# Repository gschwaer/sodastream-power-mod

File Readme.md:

# SodaStream Power Mod

> Because the Internet of Things needed a smart soda maker.

There is (or was) a soda maker called "SodaStream Power". It has some buttons and LEDs and uses a servo to do the usual pushing motion that soda makers require. Mine was broken probably due to an [unfortunate design decision](#just-why--the-beginnings) (and me). So I thought: If I have to fix it by replacing the MCU either way, why not use a WIFI-enabled one? So I build a replacement PCB with an ESP8266. It even runs python! 😲

Disclaimer: It doesn't access the internet. But it could! -- But what for? Maybe I should blink the current time in morse code for each new soda, or add a cloud backend so I can better scale my soda making. 🤔😉

So what does it use WIFI for? Well, I can debug it remotely while it's standing in the kitchen. 😅

Otherwise it just does, well, make soda. Though I improved (imo) the [user interface](#ui-changes) a little.

> ℹ️ I did this project in 2019, but I rewrote the software and documentation in 2023, so some details might be lost to time.

## Hardware

The PCB was designed in KiCad and fabricated by JLCPCB in 2019.

Main components:
* MCU: `ESP8266-12F`
* I2C-Port-Expander: `PCF8574AN`
  * Note: The suffix `A` implies a different I2C base address than the version without the `A`. The non-`A` chip works as well (but needs a minor change in code). (Took me a few hours debugging before I realized I stared at the wrong data sheet.)
* 2x Hall Switch: `SI7205-B-00-IV`
* High Side Power Switch: `TPS22810DBVR`

### Known Design issues

1. In the first revision I made a mistake and wired the LEDs to $V_{in} = 6.5 V$ (with higher values for the current limiting resistor). I thought this way I could prevent wasting power in the $3.3 V$ regulator for the LED current. Yes, that was dumb, because the regulator is a linear regulator, so the resistor dumps the same amount of power. 🤦 But the LEDs wouldn't burden the regulator at least. Anyway, the actual problem was that the port expander did not have open drain ports. Instead, ports are actively driven to low and high ($3.3V$), so in the "off" state, the LEDs (+Resistor) would see $6.5V-3.3V = 3.2V$ and would just be dimmer. 😬 I fixed it by cutting a trace and botching a wire to have the LEDs use the $3.3V$ supply rail. I'm still using that version to date. In the KiCad project that mistake has been fixed. But I didn't reorder a PCB, so that change is untested.
2. I used the least sensible GPIOs (GPIO 0, 2) for IO. It worked ok in the end, though I later had a minor issue in micropython with PWM on GPIO2 after a soft reset, because GPIO2 is a boot select pin. But I was able to fix that in software and either way: in regular operation we don't soft reset.
3. I placed some components and traces beside the antenna. Probably not good, but works ok. There is unfortunately not much space for traces around this huge center cutout.

### Schematics

> ⚠️ Warning: The [KiCad project](./PCB/Sodastream/) was converted from an older KiCad version. I'm not sure if that worked ok.

For ease of use I made some screenshots of the schematics.

### Layout

I measured the holes and cutouts on the original PCB and used identical ones on my PCB so it fits in the PCB holder. The pink areas are markings for special locations in the PCB housing: Left and right areas are keep out zones for the housing's snap fit hooks. The area in the center marks where the cabling leaves the water-proof housing.

## Software

This project uses [micropython](https://github.com/micropython/micropython/) version `1.20.0` installed as per the [documentation for ESP8266](https://docs.micropython.org/en/v1.20.0/esp8266/quickref.html). Here's the command I used:
```bash
esptool.py --port "${DEV}" --baud 460800 write_flash --erase-all --flash_size=detect 0 ESP8266_GENERIC-20230426-v1.20.0.bin
```
The code in [`./src`](./src/) is compiled with `make`. You need `mpy-cross`, `pyboard.py`, and `gcc` (see [`Makefile`](./src/Makefile)).

After that we can upload the code with [micropython's `pyboard.py` tool](https://docs.micropython.org/en/v1.20.0/reference/pyboard.py.html). The configs [`./src/webrepl_cfg.py`](./src/webrepl_cfg.py) and [`./src/wifi_cfg.py`](./src/wifi_cfg.py) require some adjustments.

After that, you can access the board via WiFi in the browser at http://192.168.0.123:8266/ (or which ever IP your board got, mDNS would be an improvement here, see [Future Work](#future-work)).

### UI Changes

Iirc the vendor UI was very basic: We have 3 buttons and 3 LEDs, when you insert a bottle all LEDs light up. Then you press one of the buttons, you get a low, medium, or high dose of CO2 into the bottle. The different doses are solely achieved by opening the CO2 valve for different, fixed durations.

Of course, that is reasonable, but it's actually a not much of an improvement compared to the manual soda makers. The main drawbacks are:
1. You still need to press a button,
2. when the CO2 cylinder empties, its pressure drops. This means the simple relationship between the duration of opening the valve and the applied CO2 dose does not hold anymore.

Drawback 1. is easily mitigated by beginning to open the CO2 valve as soon as a bottle is inserted. This means I cannot select the dose beforehand. This can be remedied by allowing a change of the dose *during* the operation. (This change is only in effect for the current soda making.)

I solved drawback 2. by tracking the cylinder state. I redefined the buttons to mean *left = "less CO2"*, *right = "more CO2"* (*center = "abort/restart"*). If a selection is made after the soda making is done, it is saved for next time. So when the CO2 cylinder empties, I can adjust the valve opening duration step by step whenever a bottle is not pressured to the degree I want. I also added some more subtle functions, and a debug mode:

| Button | Held Down Before*             | Pressed While   | Pressed After    |
|--------|-------------------------------|-----------------|------------------|
| left   | (+right) reset cylinder state | less CO2 (temp) | less CO2 (saved) |
| right  | (+left) reset cylinder state  | more CO2 (temp) | more CO2 (saved) |
| middle | debug mode (WiFi)             | abort           | start again      |

Table: Effect of buttons (1) held down while inserting a bottle, (2) pressed while the soda making happens, and (3) pressed after the soda making is completed. (* If any button is held down while a bottle is inserted, the CO2 valve stays closed. So resetting the cylinder state and entering debug mode can be done without wasting CO2.)

### Issues

I ran into some issues:

WebREPL:
* It's annoying to figure out the boards IP address. I currently check my router. But mDNS would be an obvious improvement.
* I regularly forget that when logging in via WebREPL, my python code is still running. Remember: after logging in, do `ctrl+c` to end the running program.

Boot Time:
* Boot time increases every time you overwrite a python file that is loaded at boot! I assume that has something to do with the flash filesystem trying to prevent wear. Maybe it does some copy-on-write with a linked list to traverse to the latest valid chunk? idk
  * If I remember correctly (! I didn't confirm it again !), you can reset this behavior by reformatting the flash (after that you have to reupload all files):
    ```python
    import uos
    from flashbdev import bdev
    uos.VfsLfs2.mkfs(bdev)
    vfs = uos.VfsLfs2(bdev)
    uos.mount(vfs, "/")
    ```
* I am using the following boot flow: `boot.py` -...-> `main.py` -> `sprudler.mpy`. That is mainly because `boot.py` and `main.py` cannot be compiled `.mpy` files. In `boot.py` I only put everything that I want done ASAP and `main.py` only `import`s the compiled `.mpy` file. I experimented a lot while trying to bring down boot time. I did not save the experiment results, but this solution got the best results for my use-case.
* The servo has three positions: (1) valve closed & bottle unlocked, (2) valve closed & bottle locked, (3) valve open & bottle locked. In `boot.py` I move the servo to the second (2) position. While the servo is moving to that position, we load the rest of the software and regular operation begins. This reduces the effective delay until operation begins.
* To optimize the compiled `.mpy` file, I experimented with regular global constants, constants marked with `const()`, and plain inserted constants. I'm not entirely sure what worked best, because while experimenting I also stumbled upon the issue above. Iirc boot time was best with inserted constants. So I stuck with that and added a preprocessor step using regular C preprocessor defines like `#define MY_CONST 123` in `sprudler.py`. (They get slightly garbled by the `black` formatter, but meh, I just undo this in the `Makefile`. Not elegant but works ok.)

WiFi AP:
* The WiFi AP does not work on my board with micropython `1.20.0`, so I disabled it (see [issue](https://github.com/micropython/micropython/issues/9226#issuecomment-1718269312)).
  * To prevent the board from boot looping after flashing, connect via serial and spam-paste the following into the terminal (including the newline):
    ```
    import network; network.WLAN(network.AP_IF).active(False)

    ```
    After some tries it will hit after the REPL becomes ready but before the AP is set up and the boot loop stops.

PWM:
* The servo is twitching if WiFi is enabled: The ESP8266 does not have hardware PWM outputs, so micropython does software PWM. WiFi will add a lot of load, which adds occasional lag on the software PWM timer handler. Ok for me, I only use WiFi in debug mode, where I can live with some servo twitching.

## Just Why?! / The Beginnings

Why am I doing this? Well, the electronics of my soda maker "broke", here's what happened:

The original circuitry has a tilt switch. It is just a conductive ball resting on two parallel wires, thus shorting the connection. The whole thing is in a black rectangular plastic housing with enough head room so the ball can slightly move upwards. If the PCB is flipped upside down the ball will fall away from the wires (now an open circuit) and the MCU will register that.

It turns out, if the device is on, you flip it upside down, and press any button, the MCU will go into an error state and blink the LEDs. Okay fine, maybe we just don't want our precious soda on the floor. But there is **no** way to get out of this error state! Not power cycling, no combination of button presses, short and long presses, with or without a bottle inserted, I tried everything I could think of. So ... this device just bricks itself? 🙃

Side note: If you are that kind of person (like me) who wants to know how devices work, and like to open them up to find out, you sometimes move parts aside, like for example **the PCB**, and maybe even let it dangle **upside down** on the side since the cables are so short...

However, I cannot be 100% certain that this is what bricked it. But there is a tilt switch on the PCB, it's connected to the controller, and the device went into the error state once I operated it with the PCB hanging upside down. But it could have been something else I did, who knows.

Why would the manufacturer do that? Not sure, maybe it is due to a regulation? CO2 in compressed gas cylinders is actually liquid. So from what I read, if you operate the valve while the CO2 cylinder is upside down it will spill the liquid CO2 which is very cold due to the drop in pressure. Maybe they wanted (or had) to prevent this hazard. (But why permanently!?)

## Future Work

- Add mDNS, so I don't need to look up the IP address.
  - https://github.com/vaudric/micropython/tree/main/mdns
  - https://github.com/nickovs/slimDNS
- Measure bottle pressure with a pressure sensor?

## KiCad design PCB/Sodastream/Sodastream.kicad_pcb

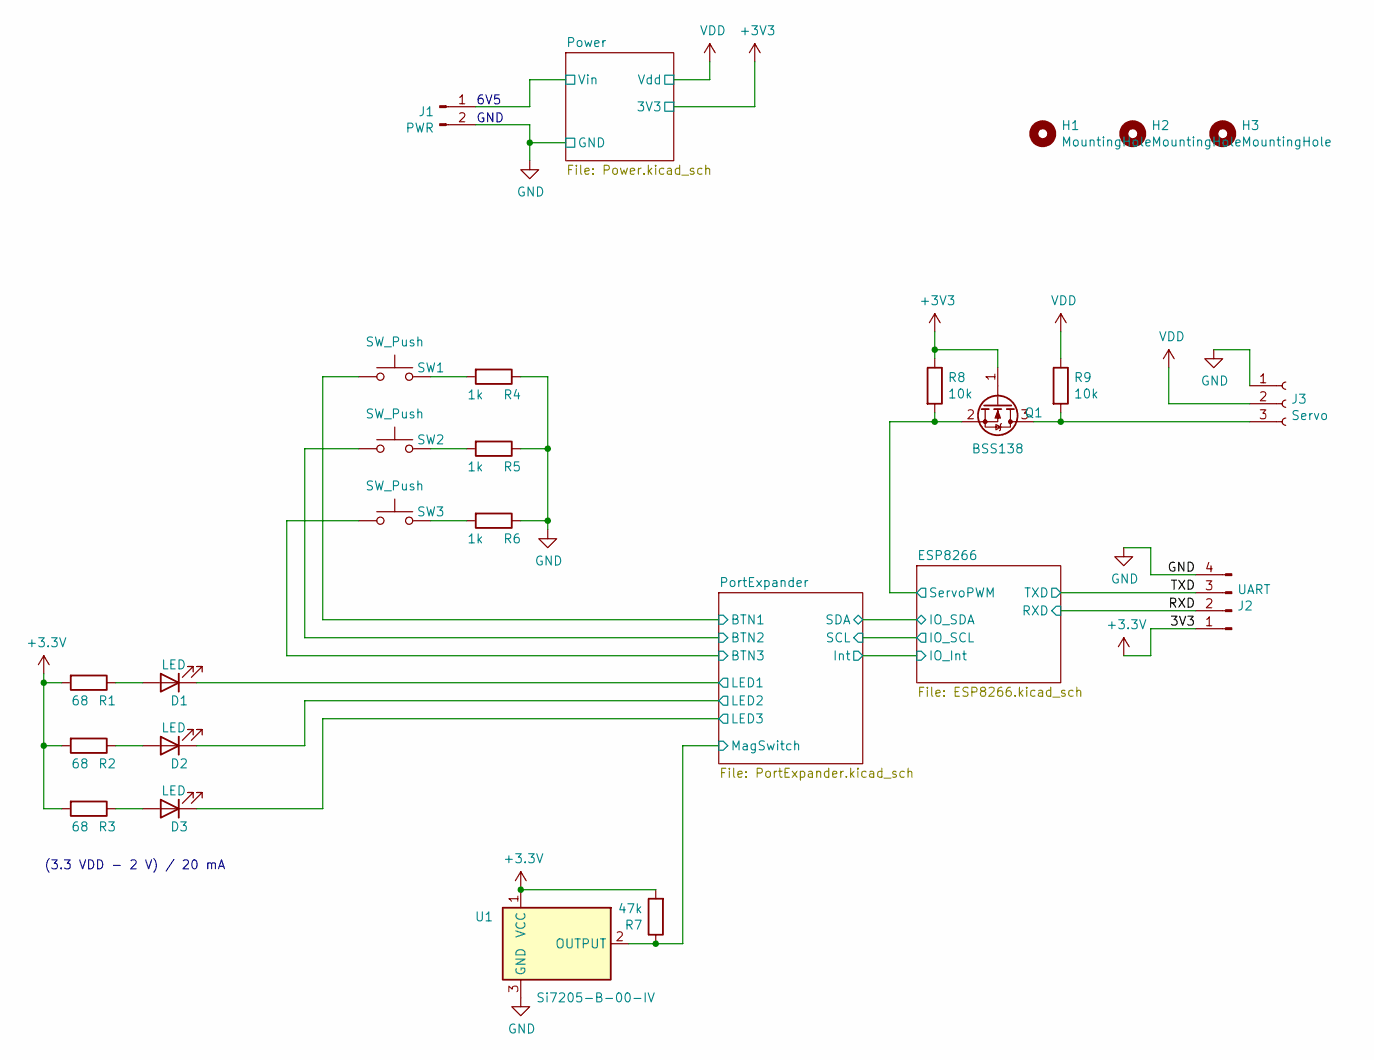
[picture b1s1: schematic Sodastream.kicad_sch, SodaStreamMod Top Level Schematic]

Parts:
D1, D2, D3: LED; LED_SMD_SideView_3.0x1.0x2.0_2+1pin
H1, H2, H3: MountingHole; MountingHole_3.2mm_M3
J1: PWR; PinHeader_1x02_P2.54mm_Vertical
J2: UART; PinHeader_1x04_P2.54mm_Vertical
J3: Servo; PinHeader_1x03_P2.54mm_Vertical
Q1: BSS138; SOT-23
R1, R2, R3: 68; R_1206_3216Metric_Pad1.42x1.75mm_HandSolder
R4, R5, R6: 1k; R_1206_3216Metric_Pad1.42x1.75mm_HandSolder
R7: 47k; R_1206_3216Metric_Pad1.42x1.75mm_HandSolder
R8, R9: 10k; R_1206_3216Metric_Pad1.42x1.75mm_HandSolder
SW1, SW2, SW3: SW_Push; SW_WE_6x6mm
U1: Si7205-B-00-IV; SOT-23

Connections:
+3V3: J2.1, Q1.1 (G), R1.2, R2.2, R3.2, R7.2, R8.1, U1.1 (VCC); also elsewhere on the board
/ESP8266/ServoPWM: Q1.2 (S), R8.2; also elsewhere on the board
/PortExpander/BTN1: SW1.1; also elsewhere on the board
/PortExpander/BTN2: SW2.1; also elsewhere on the board
/PortExpander/BTN3: SW3.1; also elsewhere on the board
/PortExpander/LED1: D1.1 (K); also elsewhere on the board
/PortExpander/LED2: D2.1 (K); also elsewhere on the board
/PortExpander/LED3: D3.1 (K); also elsewhere on the board
/PortExpander/MagSwitch: R7.1, U1.2 (OUTPUT); also elsewhere on the board
/Power/Vin: J1.1; also elsewhere on the board
/RXD: J2.2; also elsewhere on the board
/TXD: J2.3; also elsewhere on the board
GND: J1.2, J2.4, J3.1, R4.1, R5.1, R6.1, U1.3 (GND); also elsewhere on the board
unnamed: D1.2 (A), R1.1
unnamed: D2.2 (A), R2.1
unnamed: D3.2 (A), R3.1
unnamed: J3.3, Q1.3 (D), R9.2
unnamed: R4.2, SW1.2
unnamed: R5.2, SW2.2
unnamed: R6.2, SW3.2
VDD: J3.2, R9.1; also elsewhere on the board

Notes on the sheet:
(3.3 VDD - 2 V) / 20 mA
GND
6V5

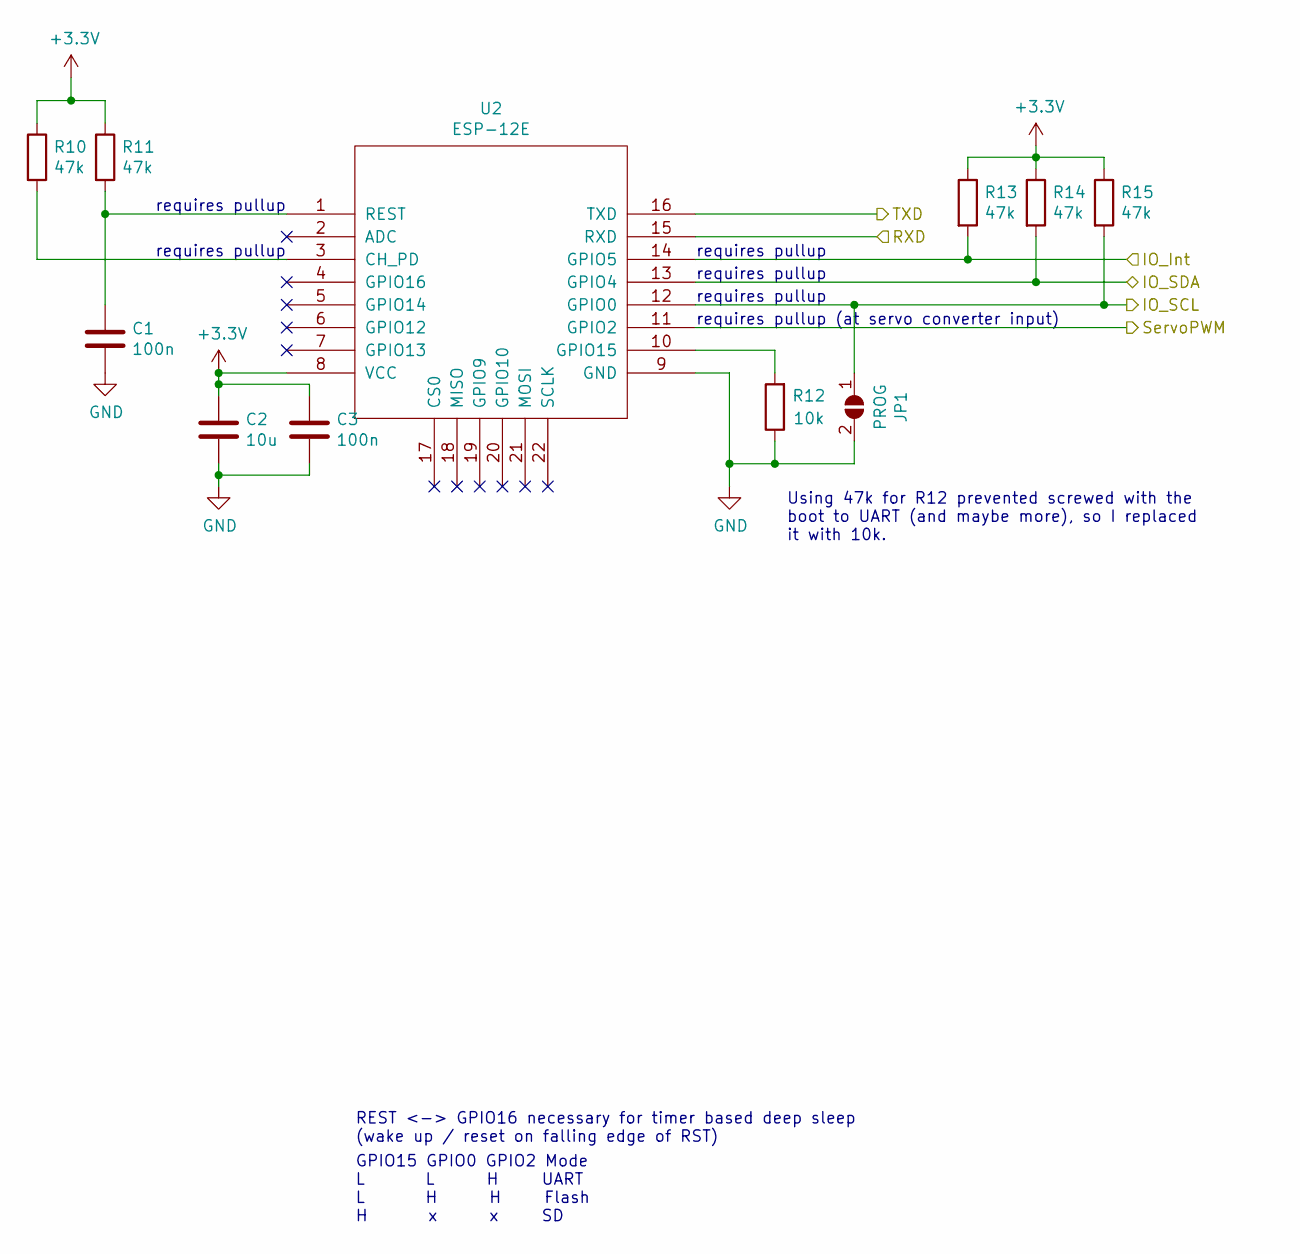
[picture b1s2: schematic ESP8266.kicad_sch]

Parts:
C1, C3: 100n; C_0805_2012Metric_Pad1.15x1.40mm_HandSolder
C2: 10u; C_0805_2012Metric_Pad1.15x1.40mm_HandSolder
JP1: PROG; SolderJumper-2_P1.3mm_Open_RoundedPad1.0x1.5mm
R10, R11, R13, R14, R15: 47k; R_1206_3216Metric_Pad1.42x1.75mm_HandSolder
R12: 10k; R_1206_3216Metric_Pad1.42x1.75mm_HandSolder
U2: ESP-12E; ESP-12E_SMD

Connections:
+3V3: C2.1, C3.1, R10.1, R11.1, R13.1, R14.1, R15.1, U2.8 (VCC); also elsewhere on the board
/ESP8266/IO_Int: R13.2, U2.14 (GPIO5); also elsewhere on the board
/ESP8266/IO_SCL: JP1.1 (A), R15.2, U2.12 (GPIO0); also elsewhere on the board
/ESP8266/IO_SDA: R14.2, U2.13 (GPIO4); also elsewhere on the board
/ESP8266/ServoPWM: U2.11 (GPIO2); also elsewhere on the board
/RXD: U2.15 (RXD); also elsewhere on the board
/TXD: U2.16 (TXD); also elsewhere on the board
GND: C1.2, C2.2, C3.2, JP1.2 (B), R12.1, U2.9 (GND); also elsewhere on the board
unnamed: C1.1, R11.2, U2.1 (REST)
unnamed: R10.2, U2.3 (CH_PD)
unnamed: R12.2, U2.10 (GPIO15)

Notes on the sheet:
requires pullup
requires pullup (at servo converter input)
Using 47k for R12 prevented screwed with the boot to UART (and maybe more), so I replaced it with 10k.
REST <-> GPIO16 necessary for timer based deep sleep (wake up / reset on falling edge of RST)
GPIO15 GPIO0 GPIO2 Mode L L H UART L H H Flash H x x SD

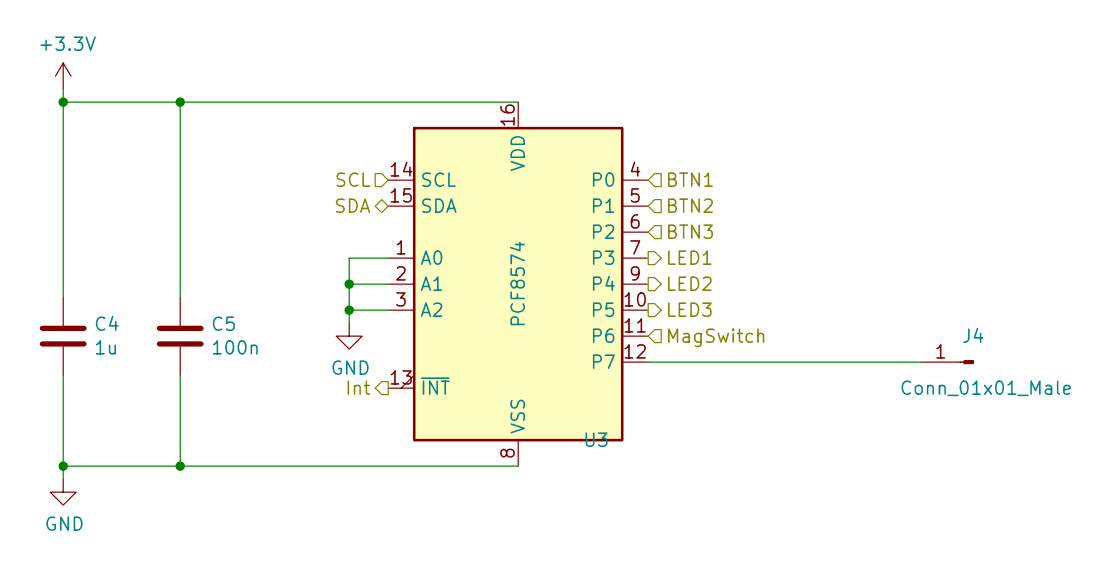
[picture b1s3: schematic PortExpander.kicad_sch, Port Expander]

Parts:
C4: 1u; C_0805_2012Metric_Pad1.15x1.40mm_HandSolder
C5: 100n; C_0805_2012Metric_Pad1.15x1.40mm_HandSolder
J4: Conn_01x01_Male; PinHeader_1x01_P2.54mm_Vertical
U3: PCF8574; DIP-16_W7.62mm

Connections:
+3V3: C4.1, C5.1, U3.16 (VDD); also elsewhere on the board
/ESP8266/IO_Int: U3.13 (~INT); also elsewhere on the board
/ESP8266/IO_SCL: U3.14 (SCL); also elsewhere on the board
/ESP8266/IO_SDA: U3.15 (SDA); also elsewhere on the board
/PortExpander/BTN1: U3.4 (P0); also elsewhere on the board
/PortExpander/BTN2: U3.5 (P1); also elsewhere on the board
/PortExpander/BTN3: U3.6 (P2); also elsewhere on the board
/PortExpander/LED1: U3.7 (P3); also elsewhere on the board
/PortExpander/LED2: U3.9 (P4); also elsewhere on the board
/PortExpander/LED3: U3.10 (P5); also elsewhere on the board
/PortExpander/MagSwitch: U3.11 (P6); also elsewhere on the board
GND: C4.2, C5.2, U3.1 (A0), U3.2 (A1), U3.3 (A2), U3.8 (VSS); also elsewhere on the board
unnamed: J4.1, U3.12 (P7)

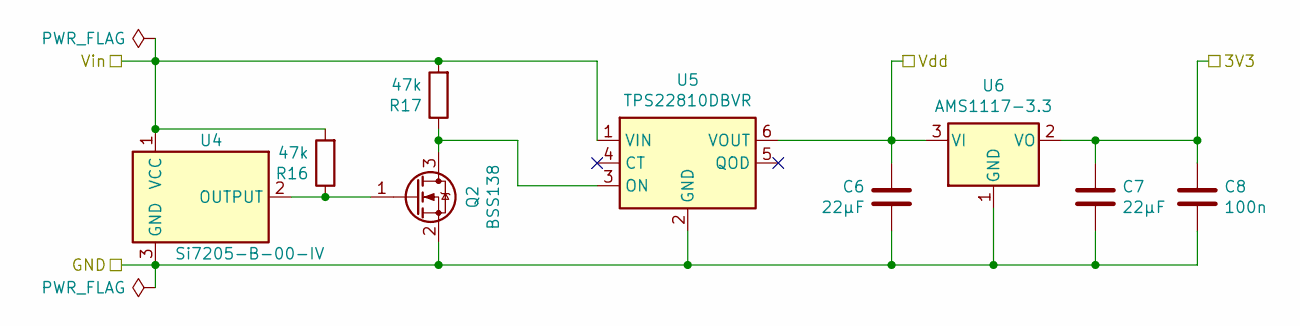
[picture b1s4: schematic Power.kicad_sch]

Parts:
C6, C7: 22µF; C_1210_3225Metric_Pad1.42x2.65mm_HandSolder
C8: 100n; C_0805_2012Metric_Pad1.15x1.40mm_HandSolder
Q2: BSS138; SOT-23
R16, R17: 47k; R_1206_3216Metric_Pad1.42x1.75mm_HandSolder
U4: Si7205-B-00-IV; SOT-23
U5: TPS22810DBVR; SOT-23-6
U6: AMS1117-3.3; SOT-223-3_TabPin2

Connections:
+3V3: C7.1, C8.1, U6.2 (VO); also elsewhere on the board
/Power/Vin: R16.2, R17.2, U4.1 (VCC), U5.1 (VIN); also elsewhere on the board
GND: C6.2, C7.2, C8.2, Q2.2 (S), U4.3 (GND), U5.2 (GND), U6.1 (GND); also elsewhere on the board
unnamed: Q2.1 (G), R16.1, U4.2 (OUTPUT)
unnamed: Q2.3 (D), R17.1, U5.3 (ON)
VDD: C6.1, U5.6 (VOUT), U6.3 (VI); also elsewhere on the board

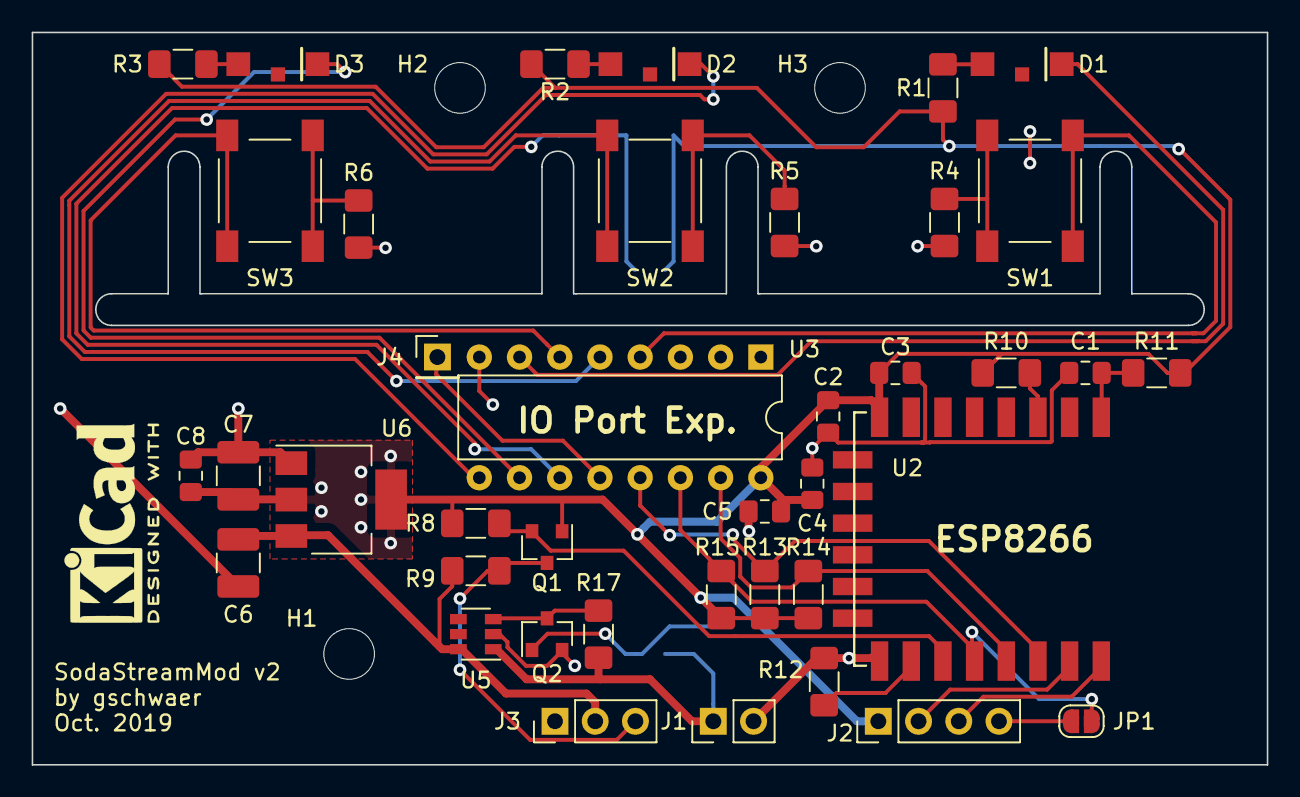
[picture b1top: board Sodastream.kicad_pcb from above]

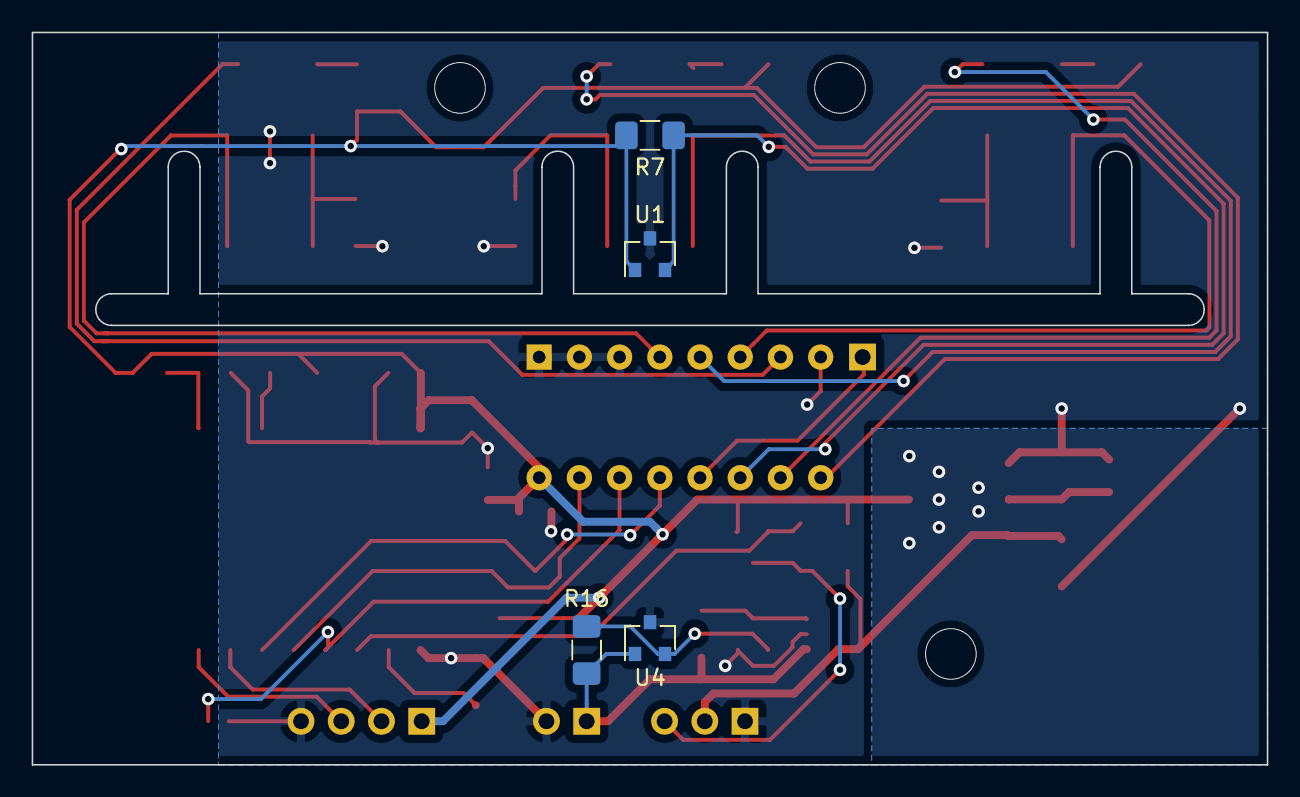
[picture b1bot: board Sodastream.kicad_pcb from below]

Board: 2 copper layers, 78.0 x 46.2 mm, 47 parts (4 on the bottom side), 30 nets.

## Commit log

2024-01-02 Add hardware layout (kicad files)
2024-01-08 Add code
2024-01-08 Add software documentation
